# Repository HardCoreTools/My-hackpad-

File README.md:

# My-hackpad
A custom macropad I designed from scratch for Hack Club's Hackpad program. It's a small programmable keypad for shortcuts and macros, built to learn PCB design, embedded firmware, and CAD along the way. 

## Features
 
- programmable keys with remappable macros
- Custom PCB designed in KiCad
- Custom firmware ([QMK / KMK])
- Custom 3D-printable case designed in Fusion 360 
- [OLED display / rotary encoder.]

## Images
 
| Schematic | PCB | Case |
|-----------|-----|------|
|  |  |  |

AND A HEADS UP- so idk how to use kicad so i imported the project to easyeda so im gonna put the easyeda files to the pcb root so im soryy and its one of my first projects so pls be kind. TY

 ## Bill of Materials
- 9x Cherry MX Switches
- 1x XIAO RP2040
- 9x Blank DSA Keycaps
- 9x 1N4148 Diodes.
- 4x M3x16 Bolt
- 4x M3 Heatset
- 1x OLED display
- 1x rotary encoder
- 1x case base
- 1x case top

## Repo Structure
 
```
.
├── pcb/         # EasyEDA schematic and board files
├── firmware/    # Microcontroller code
├── case/        # CAD files and STL/STEP exports
├── images/      # Screenshots and renders
└── README.md
```

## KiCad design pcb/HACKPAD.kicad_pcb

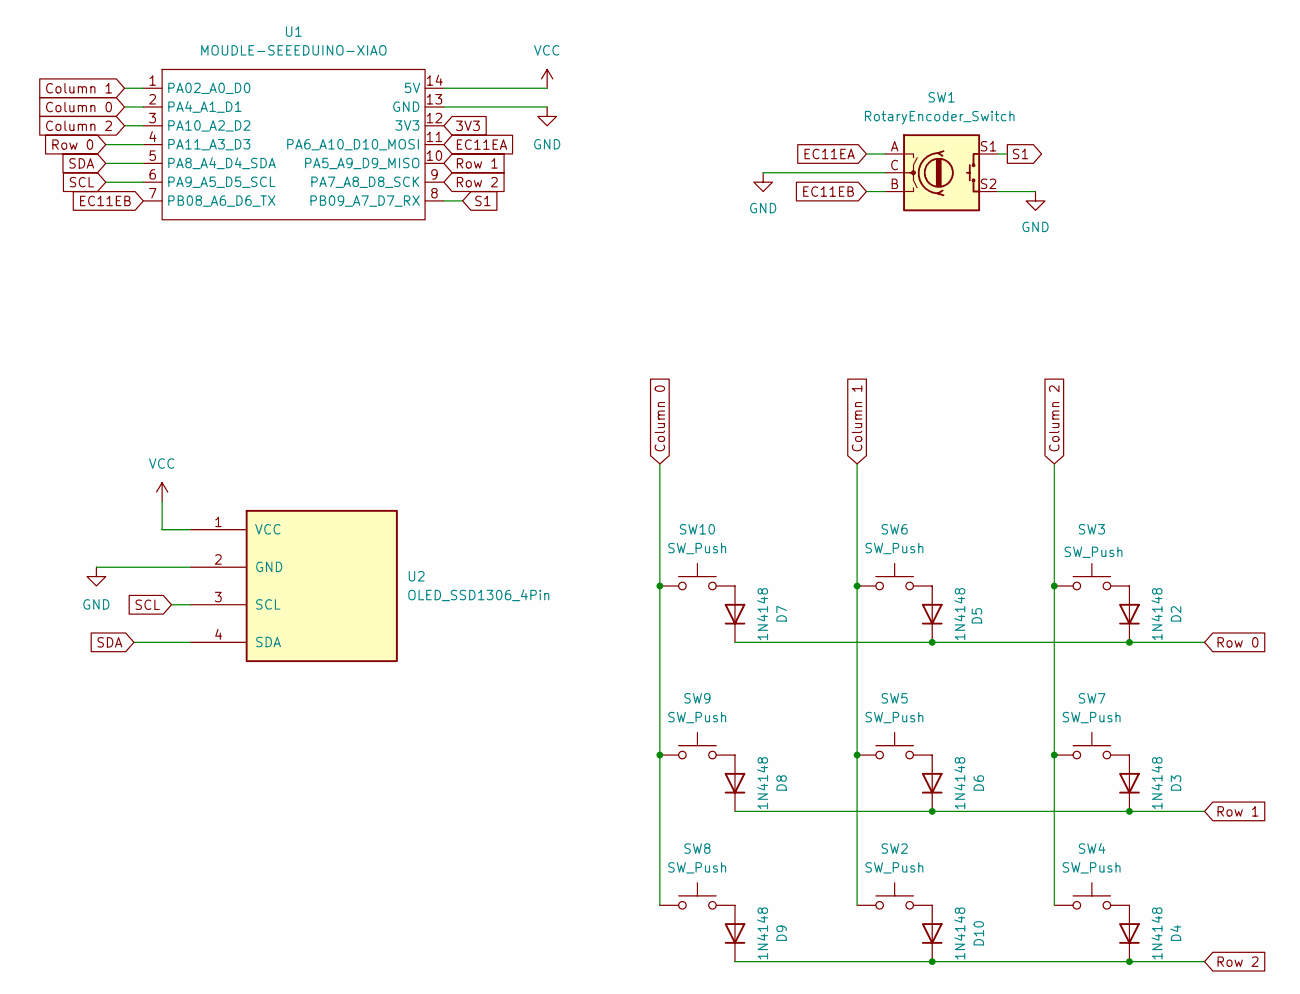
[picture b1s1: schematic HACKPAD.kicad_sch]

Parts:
D2, D3, D4, D5, D6, D7, D8, D9, D10: 1N4148; D_DO-35_SOD27_P7.62mm_Horizontal
SW1: RotaryEncoder_Switch; RotaryEncoder_Alps_EC11E-Switch_Vertical_H20mm
SW2, SW3, SW4, SW5, SW6, SW7, SW8, SW9, SW10: SW_Push; SW_Cherry_MX_1.00u_PCB
U1: MOUDLE-SEEEDUINO-XIAO; XIAO-Generic-Hybrid-14P-2.54-21X17.8MM
U2: OLED_SSD1306_4Pin; SSD1306-0.91-OLED-4pin-128x32

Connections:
3V3: U1.12 (3V3)
Column 0: SW8.1, SW9.1, SW10.1, U1.2 (PA4_A1_D1)
Column 1: SW2.1, SW5.1, SW6.1, U1.1 (PA02_A0_D0)
Column 2: SW3.1, SW4.1, SW7.1, U1.3 (PA10_A2_D2)
EC11EA: SW1.A, U1.11 (PA6_A10_D10_MOSI)
EC11EB: SW1.B, U1.7 (PB08_A6_D6_TX)
GND: SW1.C, SW1.S2, U1.13 (GND), U2.2 (GND)
unnamed: D2.2 (A), SW3.2
unnamed: D3.2 (A), SW7.2
unnamed: D4.2 (A), SW4.2
unnamed: D5.2 (A), SW6.2
unnamed: D6.2 (A), SW5.2
unnamed: D7.2 (A), SW10.2
unnamed: D8.2 (A), SW9.2
unnamed: D9.2 (A), SW8.2
unnamed: D10.2 (A), SW2.2
Row 0: D2.1 (K), D5.1 (K), D7.1 (K), U1.4 (PA11_A3_D3)
Row 1: D3.1 (K), D6.1 (K), D8.1 (K), U1.10 (PA5_A9_D9_MISO)
Row 2: D4.1 (K), D9.1 (K), D10.1 (K), U1.9 (PA7_A8_D8_SCK)
S1dfhd: SW1.S1, U1.8 (PB09_A7_D7_RX)
SCL: U1.6 (PA9_A5_D5_SCL), U2.3 (SCL)
SDA: U1.5 (PA8_A4_D4_SDA), U2.4 (SDA)
VCC: U1.14 (5V), U2.1 (VCC)

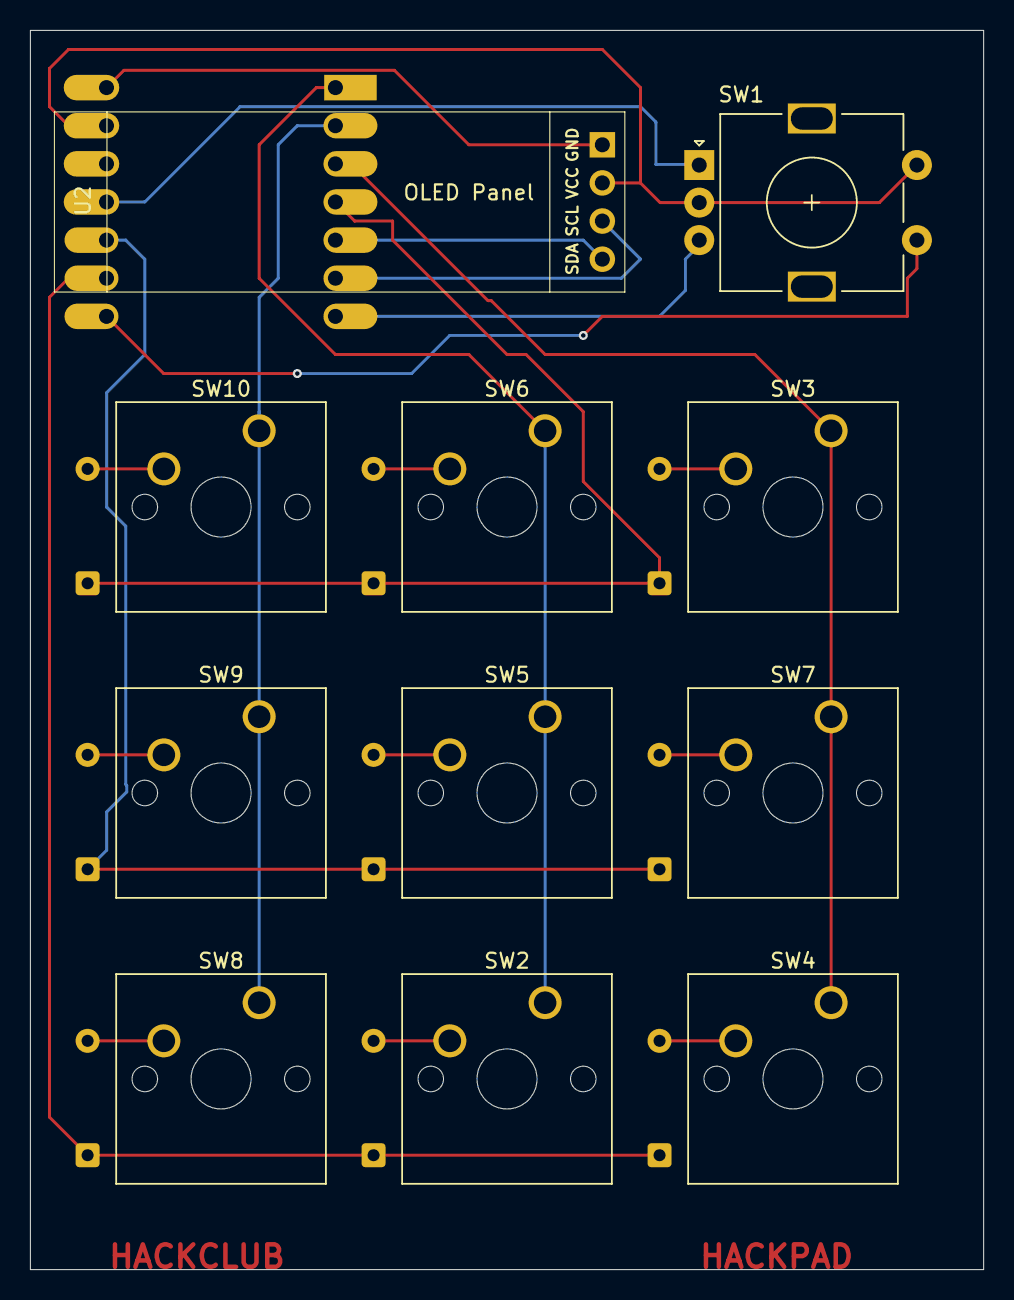
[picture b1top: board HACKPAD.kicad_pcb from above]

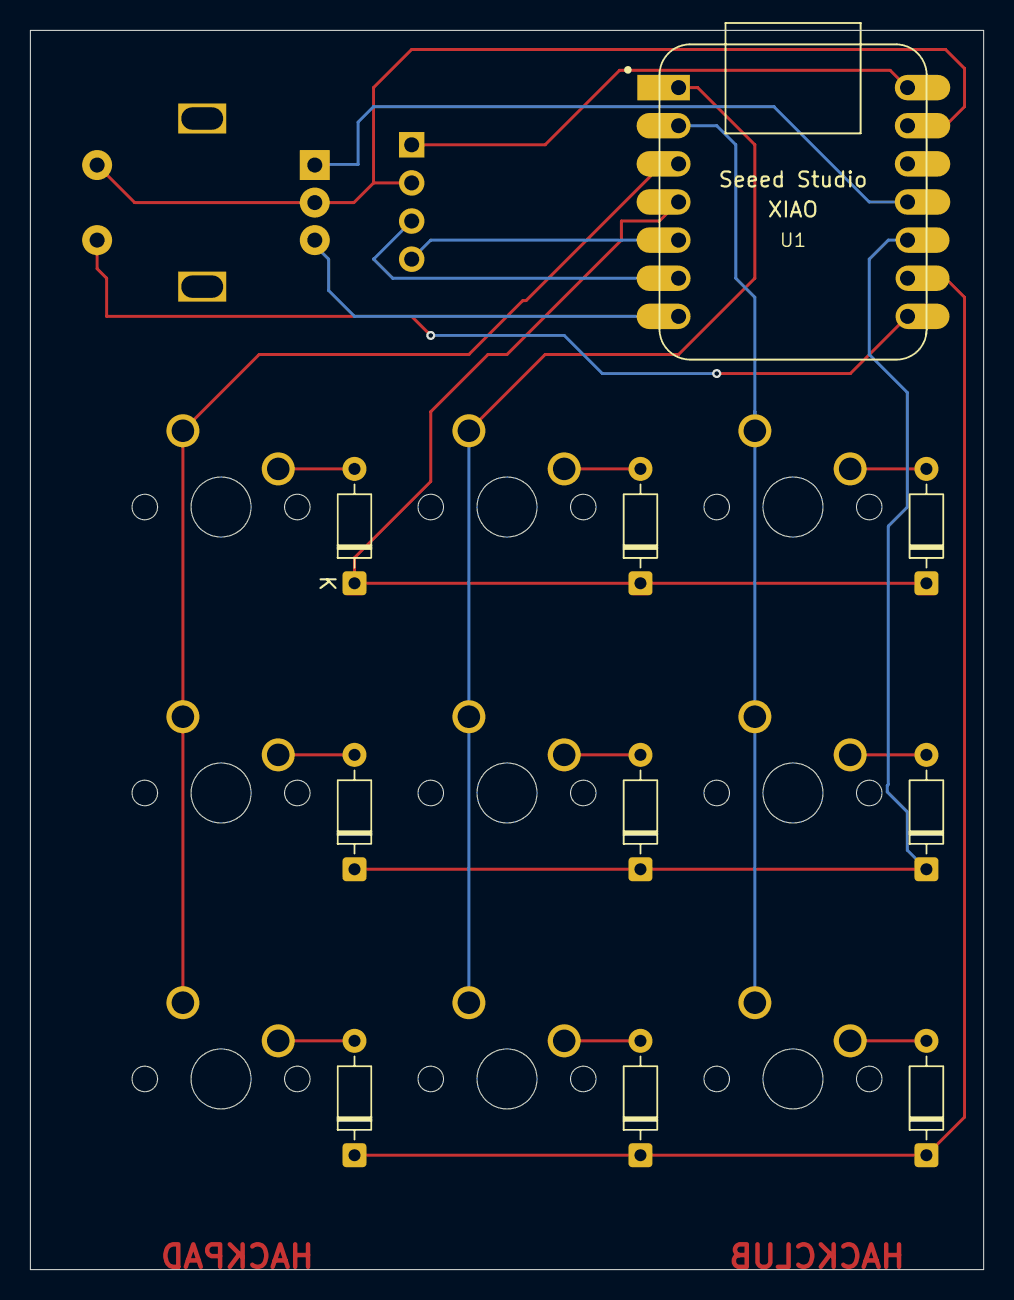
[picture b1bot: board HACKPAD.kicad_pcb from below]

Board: 2 copper layers, 63.5 x 82.6 mm, 21 parts (10 on the bottom side), 22 nets.
